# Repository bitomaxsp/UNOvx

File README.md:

# UNOvx
Arduino-like ATMega328 board

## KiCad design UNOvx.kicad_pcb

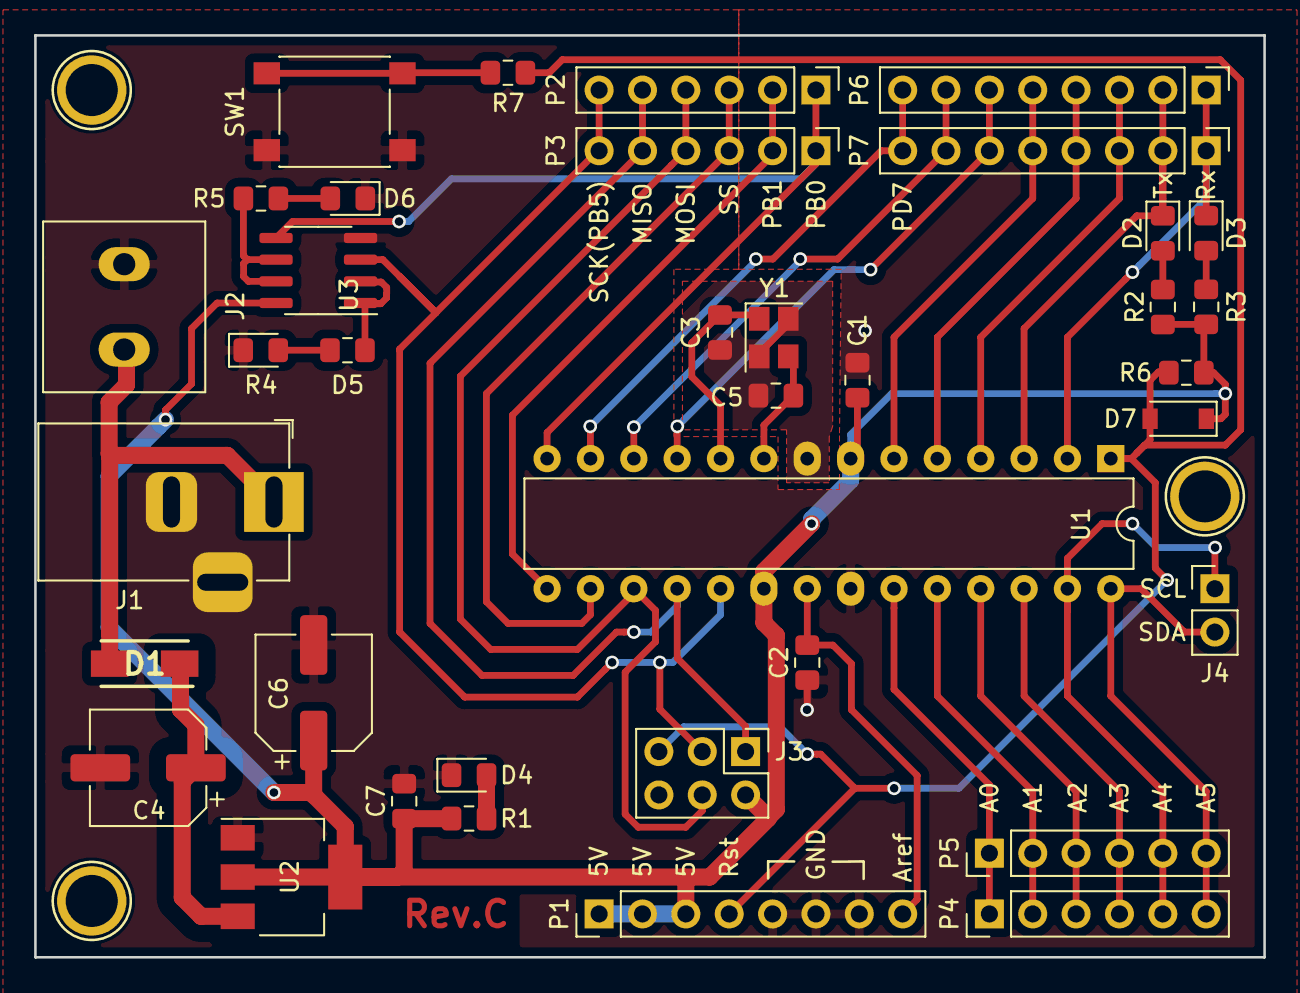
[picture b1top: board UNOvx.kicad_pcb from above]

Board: 2 copper layers, 72.0 x 54.0 mm, 40 parts (0 on the bottom side), 36 nets.

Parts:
C1, C2, C7: 100nF; C_0805_2012Metric_Pad1.15x1.40mm_HandSolder
C3, C5: 30pF; C_0805_2012Metric_Pad1.15x1.40mm_HandSolder
C4, C6: 47uF; CP_Elec_6.3x5.9
D1: M7; DIOM5127X229N
D2: YellowTx; LED_0805_2012Metric_Pad1.15x1.40mm_HandSolder
D3: YellowRx; LED_0805_2012Metric_Pad1.15x1.40mm_HandSolder
D4: Red; LED_0805_2012Metric_Pad1.15x1.40mm_HandSolder
D5, D6: Yellow; LED_0805_2012Metric_Pad1.15x1.40mm_HandSolder
D7: 1N4148W; D_SOD-123
J1: Barrel_Jack_Switch; BarrelJack_Horizontal
J2: Conn_01x02; MKDSN-2.5-1734656
J3: Conn_02x03_Odd_Even; PinHeader_2x03_P2.54mm_Vertical
J4: I2C/TWI; PinHeader_1x02_P2.54mm_Vertical
P1: Power; PinHeader_1x08_P2.54mm_Vertical
P2, P3: Digital PB; PinHeader_1x06_P2.54mm_Vertical
P4, P5: Analog PC; PinHeader_1x06_P2.54mm_Vertical
P5#2, P7, P7#3: CONN_01X01; Arduino_1pin
P6, P7#2: Digital PD; PinHeader_1x08_P2.54mm_Vertical
R1, R2, R3, R4, R5: 1k; R_0805_2012Metric_Pad1.15x1.40mm_HandSolder
R6: 10k; R_0805_2012Metric_Pad1.15x1.40mm_HandSolder
R7: 330; R_0805_2012Metric_Pad1.15x1.40mm_HandSolder
SW1: SW_Push; SW_Push_1P1T_NO_6x6mm_H9.5mm
U1: ATmega328P-PU; DIP-28_W7.62mm
U2: NCP1117-5.0_SOT223; SOT-223-3_TabPin2
U3: LM358; SOIC-8_3.9x4.9mm_P1.27mm
Y1: 16MHz; Crystal_SMD_Abracon_ABM8G-4Pin_3.2x2.5mm

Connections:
+5V: C1.2, C6.1, C7.1, D7.1, J3.2, P1.1, P1.2, P1.3, R1.1, R2.1, R3.1, R6.1, U1.7, U1.20, U2.2, U3.8
A0: P4.1, P5.1, U1.23
A1: P4.2, P5.2, U1.24
A2: P4.3, P5.3, U1.25
A3: P4.4, P5.4, U1.26
A4(SDA): J4.1, P4.5, P5.5, U1.27
A5(SCL): J4.2, P4.6, P5.6, U1.28
AREF: C2.2, P1.8, U1.21
GND: C1.1, C2.1, C3.1, C4.2, C5.1, C6.2, C7.2, D4.1, D5.1, D6.1, J1.2, J1.3, J2.2, J3.6, P1.5, P1.6, P1.7, SW1.2, U1.8, U1.22, U2.1, U3.4, Y1.2, Y1.4
unnamed: C4.1, D1.1, U2.3
unnamed: D1.2, J1.1, J2.1
unnamed: D2.2, R2.2
unnamed: D3.2, R3.2
unnamed: D4.2, R1.2
unnamed: D5.2, R4.2
unnamed: D6.2, R5.2
unnamed: R4.1, U3.1, U3.2
unnamed: R5.1, U3.6, U3.7
unnamed: R7.1, SW1.1
PB0(8): P2.1, P3.1, U1.14, U3.5
PB1(9): P2.2, P3.2, U1.15
PB2(SS): P2.3, P3.3, U1.16
PB3(MOSI): J3.4, P2.4, P3.4, U1.17
PB4(MISO): J3.1, P2.5, P3.5, U1.18
PB5(SCK): J3.3, P2.6, P3.6, U1.19, U3.3
PD2: P6.3, P7#2.3, U1.4
PD3: P6.4, P7#2.4, U1.5
PD4: P6.5, P7#2.5, U1.6
PD5: P6.6, P7#2.6, U1.11
PD6: P6.7, P7#2.7, U1.12
PD7: P6.8, P7#2.8, U1.13
Reset: D7.2, J3.5, P1.4, R6.2, R7.2, U1.1
Rx: D3.1, P6.1, P7#2.1, U1.2
Tx: D2.1, P6.2, P7#2.2, U1.3
XTAL1: C5.2, U1.9, Y1.3
XTAL2: C3.2, U1.10, Y1.1

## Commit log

2019-12-14 ADC lines
2019-12-14 Initial
2019-12-14 Fix symbol legs. Add oscillator
2019-12-14 Move power LED
2019-12-14 Route the switch
2019-12-14 remove
2019-12-14 Move the chip to allow hole
2019-12-14 All except GND plane
2019-12-14 Lock holes
2019-12-14 No power connector
2019-12-14 More lines
2019-12-14 4 layers
2019-12-14 Add lines
2019-12-14 Update packages to 0805
2019-12-14 Layout in 2 layers
    No diodes for Rx,Tx
2020-01-18 revA to rpod
2020-01-25 Remove unused file
2020-03-12 Rev. B
2020-06-19 Use proper cap values for crystal
2020-06-21 Different crystal layout with own ground
